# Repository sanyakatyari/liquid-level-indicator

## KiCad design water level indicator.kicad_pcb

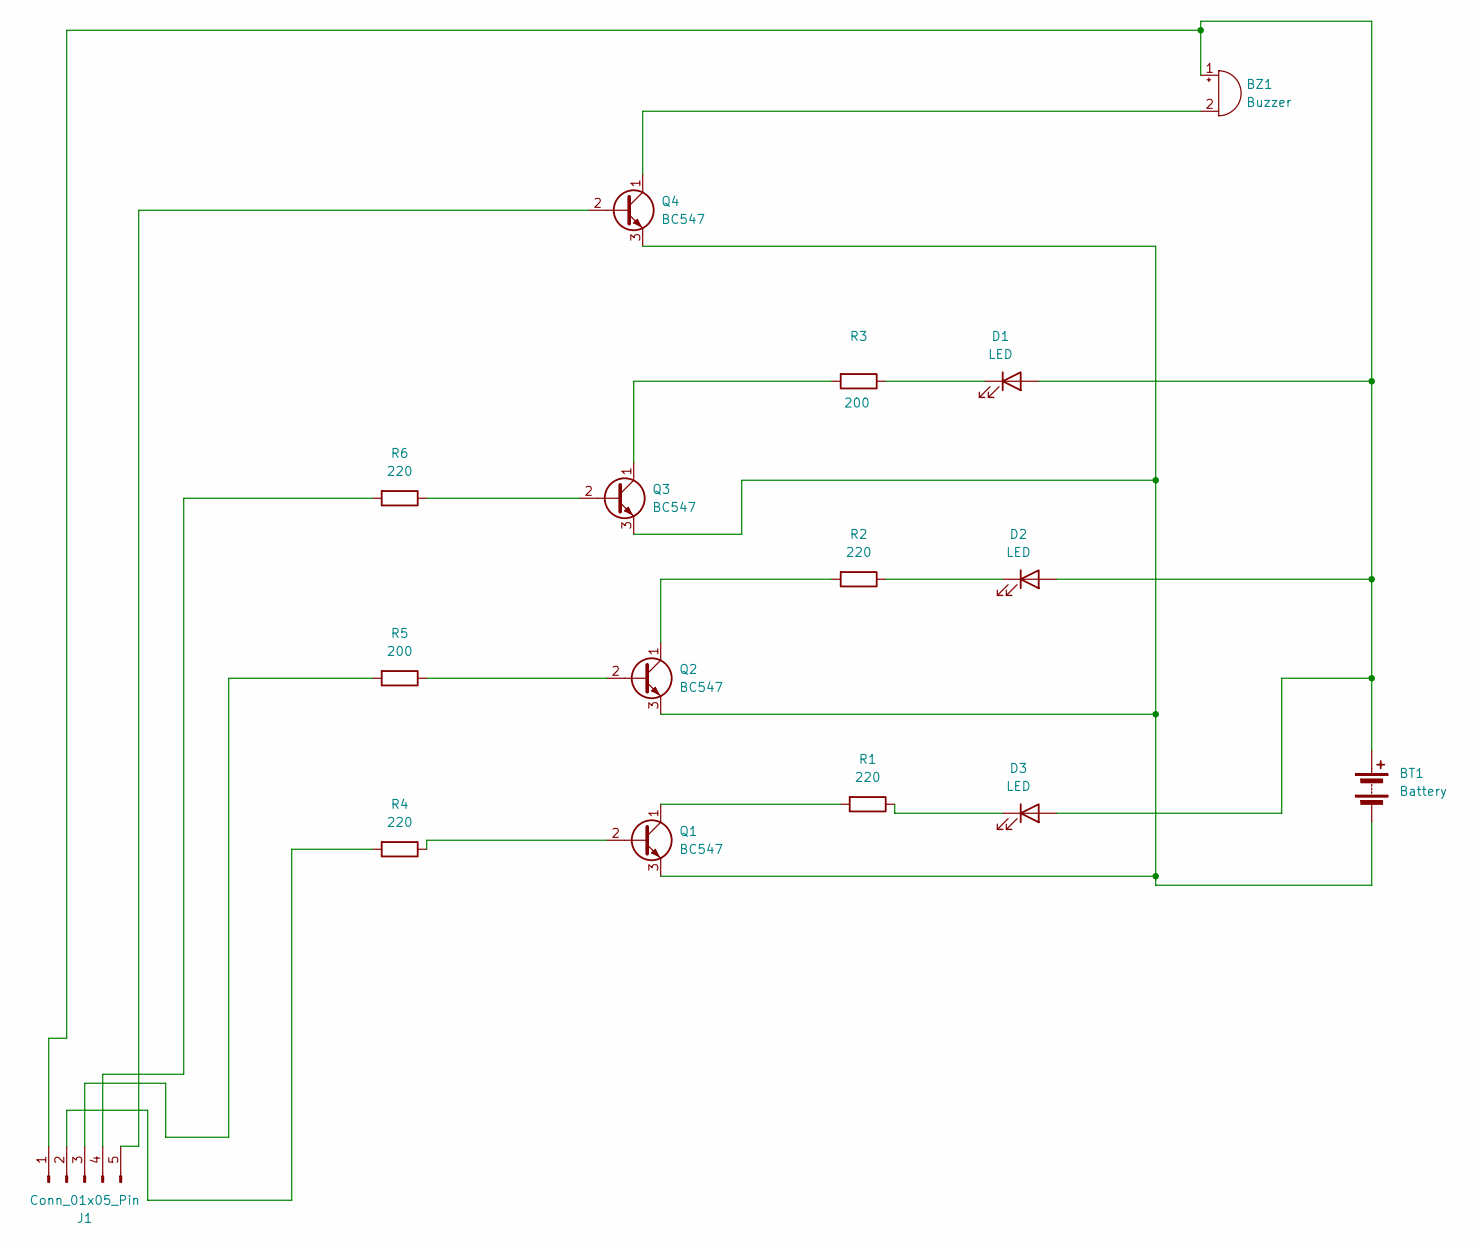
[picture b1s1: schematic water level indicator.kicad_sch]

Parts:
BT1: Battery; BatteryHolder_Keystone_2460_1xAA
BZ1: Buzzer; Buzzer_D14mm_H7mm_P10mm
D1, D2, D3: LED; LED_D5.0mm
J1: Conn_01x05_Pin; PinHeader_1x05_P2.54mm_Vertical
Q1, Q2, Q3, Q4: BC547; TO-92_Inline
R1, R2, R4, R6: 220; R_Axial_DIN0207_L6.3mm_D2.5mm_P7.62mm_Horizontal
R3, R5: 200; R_Axial_DIN0207_L6.3mm_D2.5mm_P7.62mm_Horizontal

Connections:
unnamed: BT1.1 (+), BZ1.1 (+), D1.2 (A), D2.2 (A), D3.2 (A), J1.1
unnamed: BT1.2 (-), Q1.3 (E), Q2.3 (E), Q3.3 (E), Q4.3 (E)
unnamed: BZ1.2 (-), Q4.1 (C)
unnamed: D1.1 (K), R3.1
unnamed: D2.1 (K), R2.1
unnamed: D3.1 (K), R1.1
unnamed: J1.2, R4.2
unnamed: J1.3, R5.2
unnamed: J1.4, R6.2
unnamed: J1.5, Q4.2 (B)
unnamed: Q1.2 (B), R4.1
unnamed: Q1.1 (C), R1.2
unnamed: Q2.2 (B), R5.1
unnamed: Q2.1 (C), R2.2
unnamed: Q3.2 (B), R6.1
unnamed: Q3.1 (C), R3.2

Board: 2 copper layers, 16 parts (0 on the bottom side), 16 nets, no tracks yet.

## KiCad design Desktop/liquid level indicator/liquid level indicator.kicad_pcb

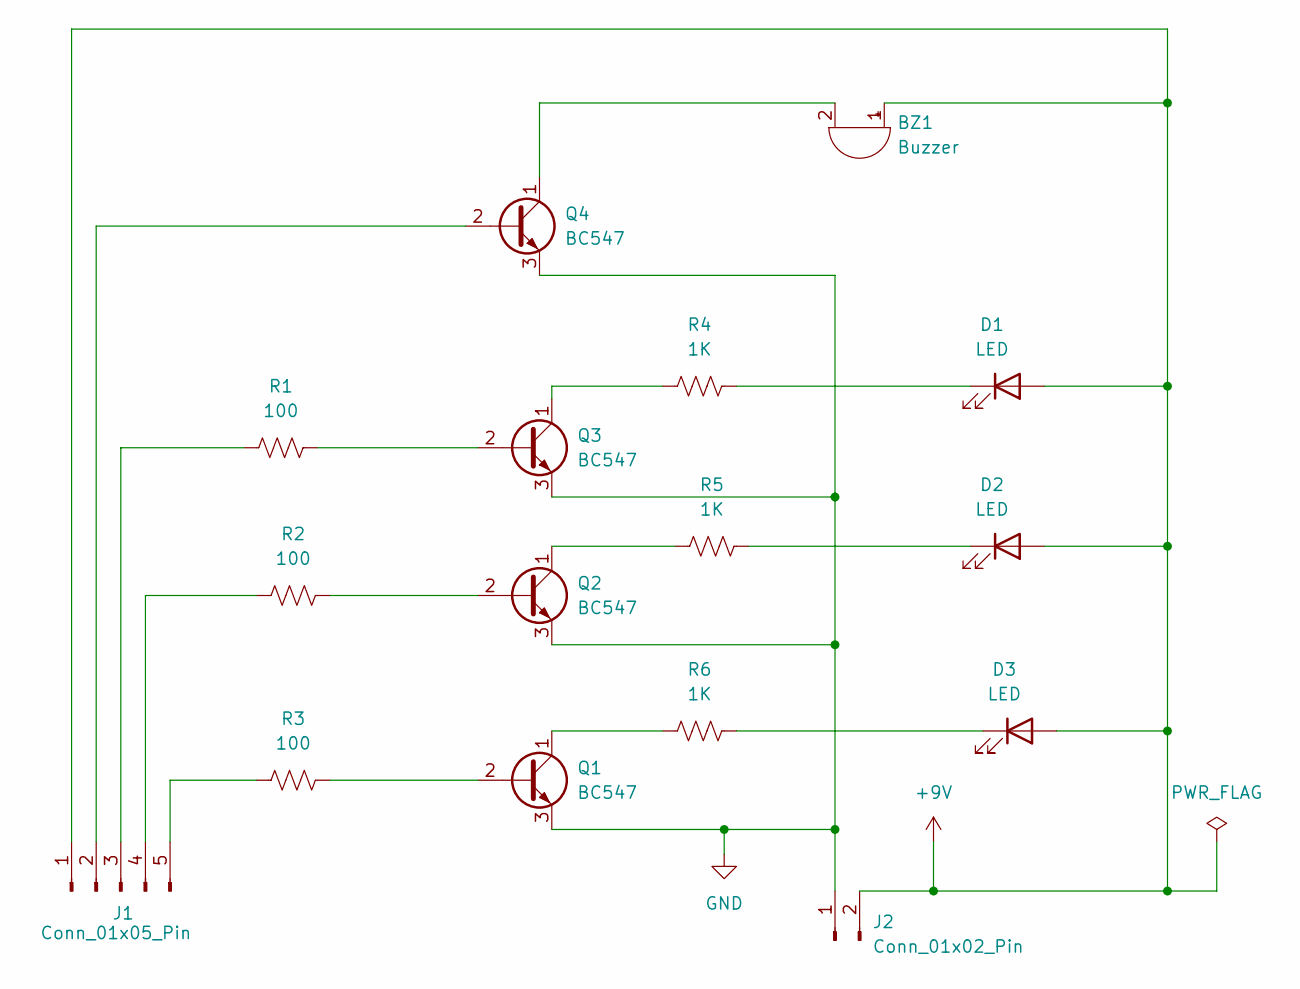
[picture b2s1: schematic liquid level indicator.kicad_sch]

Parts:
BZ1: Buzzer; Buzzer_15x7.5RM7.6
D1, D2, D3: LED; LED_D5.0mm
J1: Conn_01x05_Pin; PinHeader_1x05_P2.54mm_Vertical
J2: Conn_01x02_Pin; PinHeader_1x02_P2.54mm_Vertical
Q1, Q2, Q3, Q4: BC547; TO-92_Inline
R1, R2, R3: 100; R_Axial_DIN0207_L6.3mm_D2.5mm_P7.62mm_Horizontal
R4, R5, R6: 1K; R_Axial_DIN0207_L6.3mm_D2.5mm_P7.62mm_Horizontal

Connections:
+9V: BZ1.1 (+), D1.2 (A), D2.2 (A), D3.2 (A), J1.1, J2.2
GND: J2.1, Q1.3 (E), Q2.3 (E), Q3.3 (E), Q4.3 (E)
unnamed: BZ1.2 (-), Q4.1 (C)
unnamed: D1.1 (K), R4.2
unnamed: D2.1 (K), R5.2
unnamed: D3.1 (K), R6.2
unnamed: J1.2, Q4.2 (B)
unnamed: J1.3, R1.1
unnamed: J1.4, R2.1
unnamed: J1.5, R3.1
unnamed: Q1.2 (B), R3.2
unnamed: Q1.1 (C), R6.1
unnamed: Q2.2 (B), R2.2
unnamed: Q2.1 (C), R5.1
unnamed: Q3.2 (B), R1.2
unnamed: Q3.1 (C), R4.1

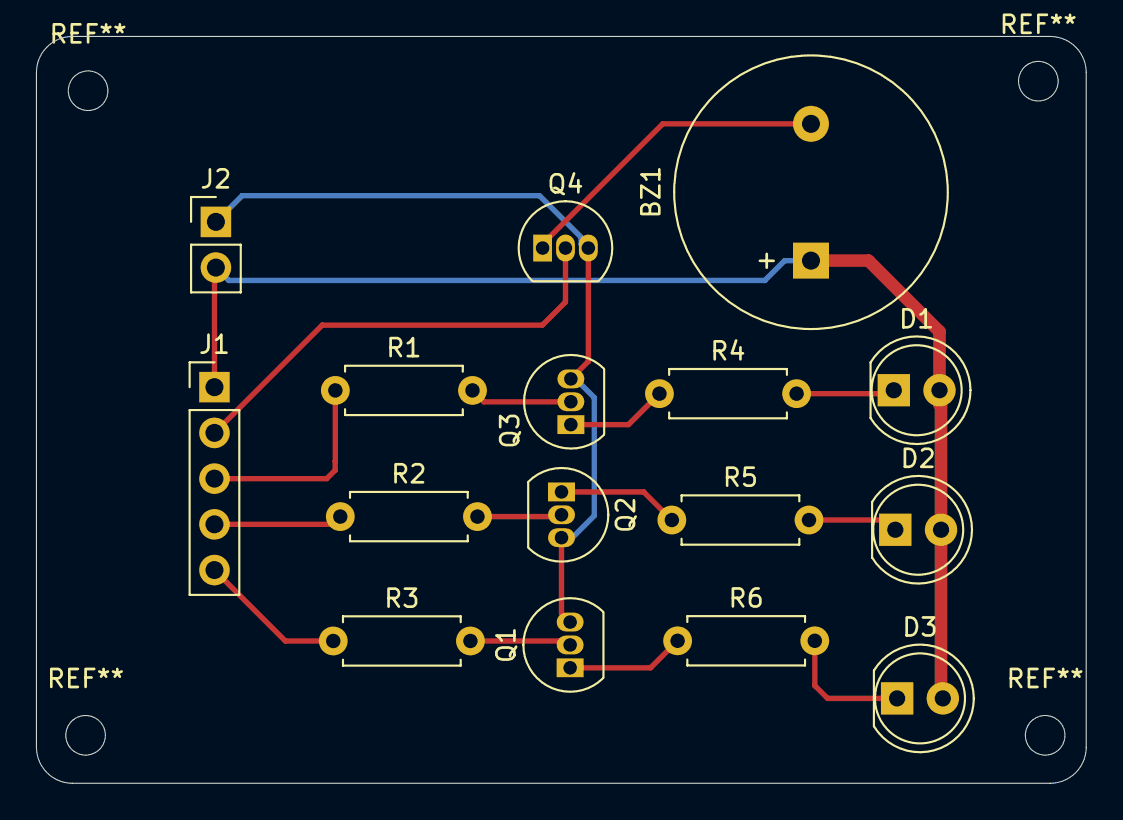
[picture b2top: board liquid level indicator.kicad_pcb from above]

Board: 2 copper layers, 58.3 x 41.5 mm, 16 parts (0 on the bottom side), 16 nets.
